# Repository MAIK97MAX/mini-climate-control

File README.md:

# MMD Smart Home Solutions – Smart Climate Control

Embedded climate-control system developed as part of our HTL diploma project.

The system uses an ESP32-S3 as the central controller to monitor temperature sensors and control a thermoelectric heating/cooling unit and ventilation fans.

## Features

- ESP32-S3 central controller
- Thermoelectric heating and cooling
- PWM fan control
- Wireless temperature sensors
- Local OLED status display
- Wi-Fi web interface
- USB-C and 12 V power input
- Custom 4-layer PCB

## Repository

This repository contains the hardware design, firmware and related project files.

## Authors

Malik Jukic
David Sayfutdinov
Muhammet Karpuz

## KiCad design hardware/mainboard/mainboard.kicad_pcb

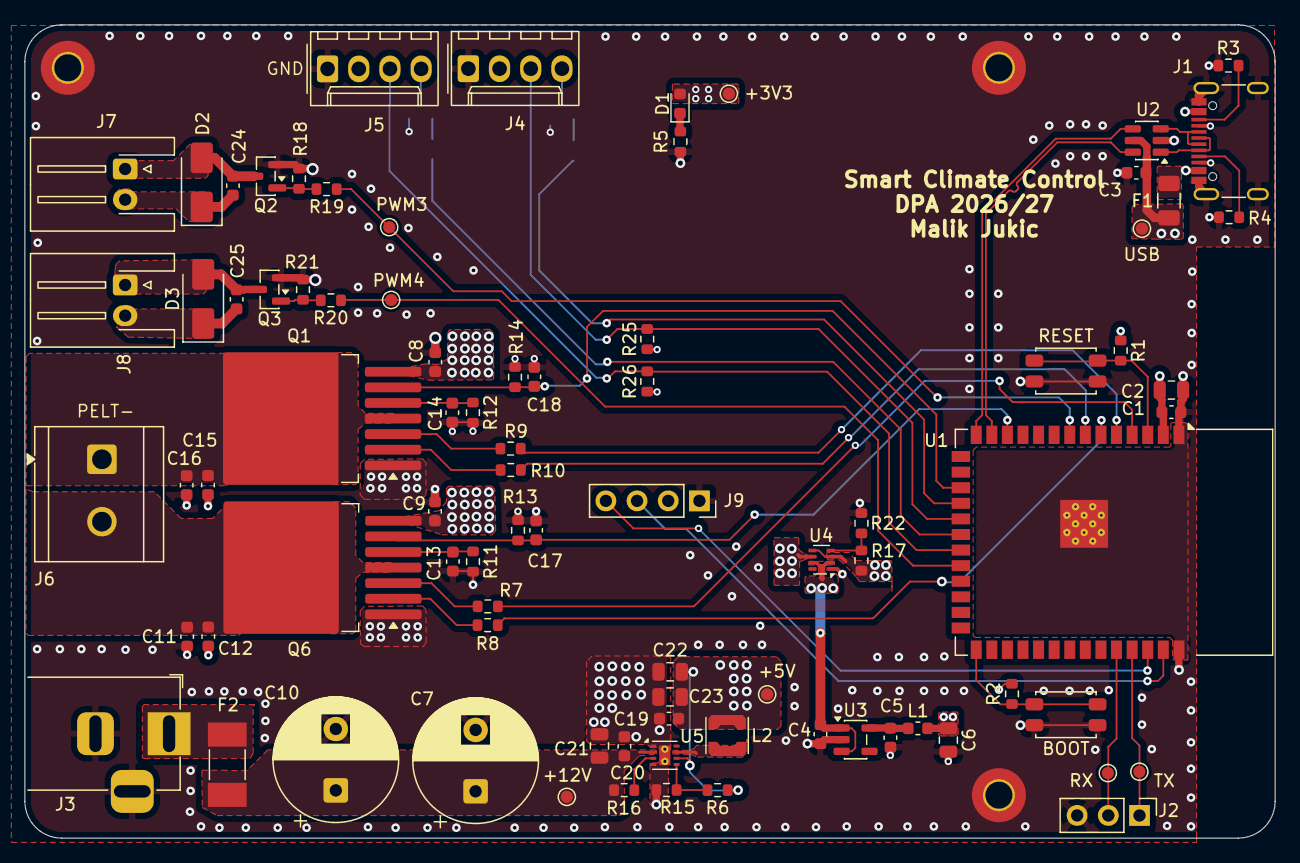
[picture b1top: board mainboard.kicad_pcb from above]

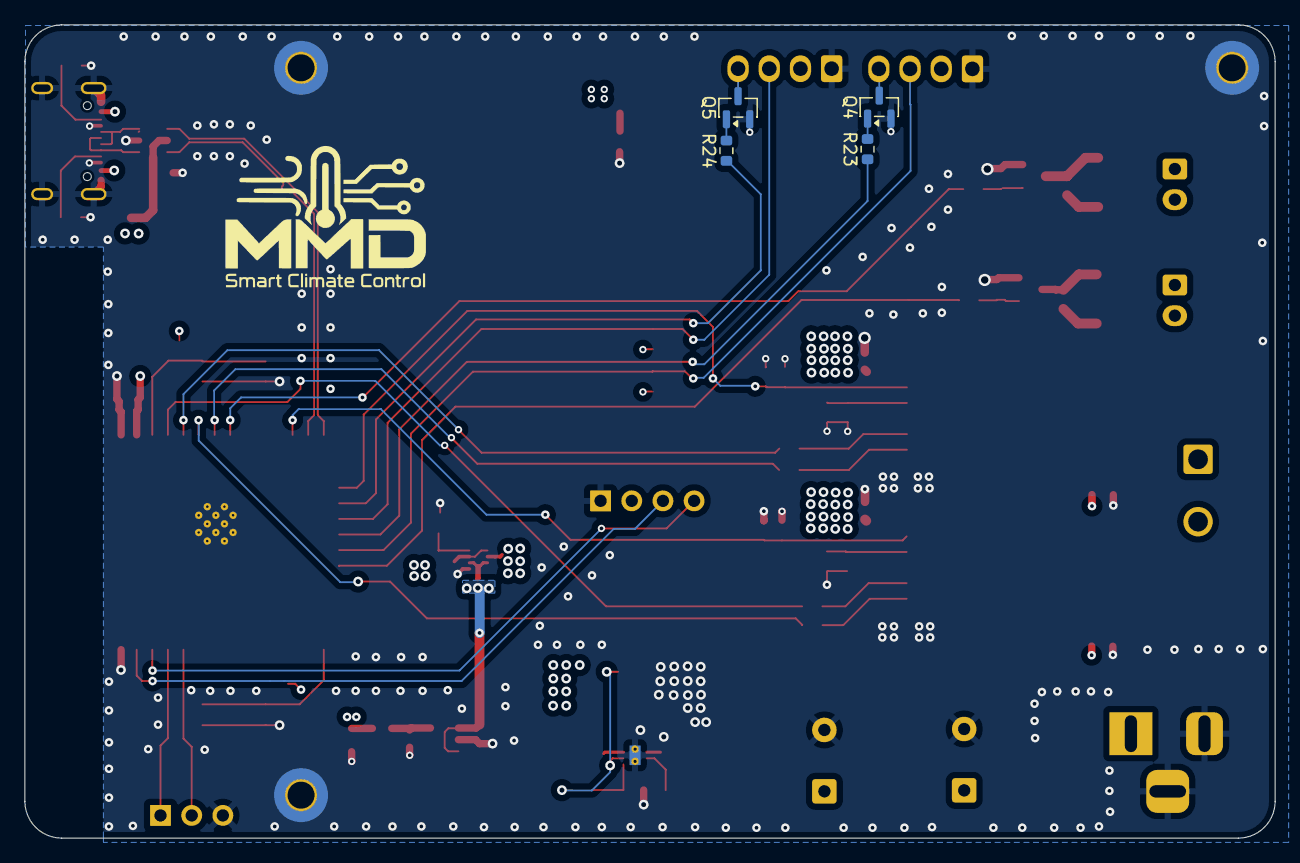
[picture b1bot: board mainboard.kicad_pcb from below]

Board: 4 copper layers, 101.9 x 66.3 mm, 91 parts (4 on the bottom side), 54 nets.

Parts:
+5V: TestPoint_5V; TestPoint_Pad_D1.0mm
+12V: TestPoint_12V; TestPoint_Pad_D1.0mm
BOOT: SW_Push; SW_SPST_EVQP2_MiddlePushTravel_H2.5mm
C1, C3, C4, C5, C8, C9, C13, C14, C19, C20, C24, C25: 100nF; C_0603_1608Metric
C2, C6, C21: 10uF; C_0805_2012Metric
C7, C10: 470uF; CP_Radial_D10.0mm_P5.00mm
C11, C12, C15, C16: 220nF; C_0603_1608Metric
C17, C18: 1nF; C_0603_1608Metric
C22, C23: 22uF; C_0805_2012Metric
D1: LED; LED_0603_1608Metric
D2, D3: SS24; D_SMA
F1: 750mA; Fuse_1206_3216Metric
F2: 6.3A; Fuse_Littelfuse-NANO2-451_453
H1, H2, H3: MountingHole_Pad; MountingHole_2.2mm_M2_Pad_TopBottom
J1: USB_C_Receptacle_USB2.0_16P; USB_C_Receptacle_G-Switch_GT-USB-7010ASV
J2: Conn_01x03_Pin; PinHeader_1x03_P2.54mm_Vertical
J3: Barrel_Jack_MountingPin; BarrelJack_Horizontal
J4, J5: Conn_01x04_Socket; Molex_KK-254_AE-6410-04A_1x04_P2.54mm_Vertical
J6: Screw_Terminal_01x02; TerminalBlock_CUI_TB007-508-02_1x02_P5.08mm_Horizontal
J7, J8: Conn_01x02_Socket; JST_XH_S2B-XH-A-1_1x02_P2.50mm_Horizontal
J9: Conn_01x04_Socket; PinSocket_1x04_P2.54mm_Vertical
L1: L_Ferrite; L_0603_1608Metric
L2: 2.2uH; L_Coilcraft_LPS3010
PWM3: TestPoint_PWM3; TestPoint_Pad_D1.0mm
PWM4: TestPoint_PWM4; TestPoint_Pad_D1.0mm
Q1, Q6: BTN8982TA; TO-263-7_TabPin8
Q2, Q3, Q4, Q5: AO3400A; SOT-23
R1, R2, R6, R7, R8, R9, R10, R17, R22, R25, R26: 10k; R_0603_1608Metric
R3, R4: 5k1; R_0603_1608Metric
R5, R19, R20, R23, R24: 220; R_0603_1608Metric
R11, R12: 510; R_0603_1608Metric
R13, R14: 1k; R_0603_1608Metric
R15: 52k3; R_0603_1608Metric
R16, R18, R21: 100k; R_0603_1608Metric
RESET: SW_Push; SW_SPST_EVQP2_MiddlePushTravel_H2.5mm
RX: TestPoint_RX; TestPoint_Pad_D1.0mm
TP6: TestPoint_3V3; TestPoint_Pad_D1.0mm
TX: TestPoint_TX; TestPoint_Pad_D1.0mm
U1: ESP32-S3-WROOM-1
U2: USBLC6-2SC6; SOT-23-6
U3: AP2112K-3.3; SOT-23-5
U4: TPS2116DRL; SOT-583-8
U5: TPS62161DSG; WSON-8-1EP_2x2mm_P0.5mm_EP0.9x1.6mm_ThermalVias
USB: TestPoint_VBUS; TestPoint_Pad_D1.0mm

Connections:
+3V3: C1.1, C2.1, C6.1, D1.2 (A), J9.2, L1.2, R1.1, R2.1, R25.1, R26.1, TP6.1, U1.2 (3V3)
+5V: +5V.1, C19.1, C22.1, C23.1, L2.2, R6.1, R17.2, U4.3 (VIN1), U4.5 (MODE), U5.6 (VOS)
+12V: +12V.1, C7.1, C8.1, C9.1, C10.1, C11.1, C15.1, C20.1, C21.1, C24.1, C25.1, D2.1 (K), D3.1 (K), F2.2, J4.2, J5.2, J7.2, J8.2, Q1.7, Q6.7, R16.1, U5.2 (VIN)
/5V_SEL: C4.1, U3.1 (VIN), U3.3 (EN), U4.2 (VOUT), U4.7 (VOUT)
/12V: F2.1, J3.1
/BOOT: BOOT.2, R2.2, U1.27 (IO0)
/CC1: J1.A5 (CC1), R4.2
/CC2: J1.B5 (CC2), R3.2
/D+: J1.A6 (D+), J1.B6 (D+), U2.3 (I/O2)
/D-: J1.A7 (D-), J1.B7 (D-), U2.1 (I/O1)
/EN: R16.2, U5.3 (EN)
/FAN_GATE: Q2.1 (G), R18.1, R19.2
/FAN_GATE2: Q3.1 (G), R20.2, R21.1
/FAN_GND: C24.2, D2.2 (A), J7.1, Q2.3 (D)
/FAN_GND2: C25.2, D3.2 (A), J8.1, Q3.3 (D)
/FB: R6.2, R15.1, U5.5 (FB)
/GATE1: Q5.1 (G), R24.2
/GATE2: Q4.1 (G), R23.2
/IN: Q6.2 (IN), R8.2
/IN2: Q1.2 (IN), R10.2
/INH: Q6.3 (INH), R7.2
/INH2: Q1.3 (INH), R9.2
/PELT+: C11.2, C12.1, J6.2, Q6.4, Q6.8
/PELT-: C15.2, C16.1, J6.1, Q1.4, Q1.8
/PR1: R17.1, R22.1, U4.4 (PR1)
/PWM1_OUT: J4.4, Q5.3 (D)
/PWM2_OUT: J5.4, Q4.3 (D)
/RST: R1.2, RESET.2, U1.3 (EN)
/RX: J2.2, RX.1, U1.36 (RXD0)
/SR: C13.1, Q6.5 (SR), R11.1
/SR2: C14.1, Q1.5 (SR), R12.1
/SW: L2.1, U5.7 (SW)
/TX: J2.1, TX.1, U1.37 (TXD0)
/VBUS: F1.1, J1.A4 (VBUS), J1.A9 (VBUS), J1.B4 (VBUS), J1.B9 (VBUS)
/VBUS_1: C3.1, F1.2, U2.5 (VBUS), U4.6 (VIN2), USB.1
GND: BOOT.1, C1.2, C2.2, C3.2, C4.2, C5.2, C6.2, C7.2, C8.2, C9.2, C10.2, C12.2, C13.2, C14.2, C16.2, C17.2, C18.2, C19.2, C20.2, C21.2, C22.2, C23.2, H1.1, H2.1, H3.1, J1.A1 (GND), J1.A8 (SBU1), J1.A12 (GND), J1.B1 (GND), J1.B8 (SBU2), J1.B12 (GND), J1.S1 (SHIELD), J2.3, J3.2, J3.3, J4.1, J5.1, J9.1, Q1.1, Q2.2 (S), Q3.2 (S), Q4.2 (S), Q5.2 (S), Q6.1, R3.1, R4.1, R5.2, R11.2, R12.2, R13.2, R14.2, R15.2, R18.2, R21.2, R22.2, RESET.1, U1.1 (GND), U1.40 (GND), U1.41 (GND), U2.2 (GND), U3.2 (GND), U4.1 (GND), U5.1 (PGND), U5.4 (AGND), U5.9 (PAD)
INH_1: R7.1, U1.4 (IO4)
INH_2: R9.1, U1.5 (IO5)
IS_1: C17.1, Q6.6 (IS), R13.1, U1.12 (IO8)
IS_2: C18.1, Q1.6 (IS), R14.1, U1.17 (IO9)
unnamed: D1.1 (K), R5.1
unnamed: C5.1, L1.1, U3.5 (VOUT)
PELT_H1: R8.1, U1.6 (IO6)
PELT_H2: R10.1, U1.7 (IO7)
PWM1: R24.1, U1.18 (IO10)
PWM2: R23.1, U1.20 (IO12)
PWM3: PWM3.1, R19.1, U1.8 (IO15)
PWM4: PWM4.1, R20.1, U1.22 (IO14)
SCL: J9.3, U1.39 (IO1)
SDA: J9.4, U1.38 (IO2)
TACH1: J4.3, R25.2, U1.19 (IO11)
TACH2: J5.3, R26.2, U1.21 (IO13)
USB_D+: U1.14 (USB_D+), U2.4 (I/O2)
USB_D-: U1.13 (USB_D-), U2.6 (I/O1)
